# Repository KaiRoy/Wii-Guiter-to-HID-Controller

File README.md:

# HID Guitar Controller - Converting a Wii Guitar into a Windows Compatible HID Device

	<!-- Add image of the PCB -->

## Table of Contents

- [Description](#description)
- [Design](#design)
- [Current State](#current-state-of-the-project)
- [Post Project Notes](#post-project-notes)
- [Installation](#installation) <!-- Should I have Installation and Usage above or below the Design, Current State, Changes, etc? -->
- [Usage](#usage)
- [Credits](#credits)
- [License](#license)

## Description

This project aims to create a device that will take the data from a Wii Guitar Extension Controller and transmit that data to a computer as an HID Device. 

I am a fan of Guitar Hero and rhythm games in general. Guitar Hero was the first rhythm game I ever played and I played it on the Wii using the extension device that came with the game. I long sold the Wii, but I found out that there was a PC version of Guitar Hero called Clone Hero. Since I still had the extension device so I looked into connecting a Wii Remote to a windows computer. While you are able to connect a Wii controller via bluetooth to a Windows Computer it requires the use of third party uncertified drivers. This requires certain settings to turned off in Windows, such as test-signing. The downside of this is that it triggers anti-cheat softwares in competitive video games such as Valorant, making you unable to play those games with the settings turned off. Since these settings require a Computer Restart everytime they are changed, it makes it tedious to switch between games. 

Since I am an electrical engineering major, I decided to make a device that will practically replace the Wii Remote and be able to read the controller inputs from the Wii Guitar Extension Controller and interface with windows as an HID device. I also wanted to make this a battery-powered bluetooth device to remove any cables while using the controller. 

## Design

A lot of information exists on how the Wii works including how the Wii Remote communicates with extension devices such as the Nunchuk or the Wii Guitar. The communication protocol used is a 3.3V I2C signal(s) with nearly all extension devices having an address of 0x52. By default, the data is encrypted but more ‘modern’ extension devices, such as the Wii Guitar, can be set in a decrypted communication mode using the following I2C sequence:

Start, 0xF0, 0x55, Stop, Start, 0xFB, 0x00, Stop

The data is formatted into 6 bytes with the following bit structure with the default bit value being 1 for all of the buttons, changing to 0 when the button is pressed:

SX and SY refer to the x and y-axis of the analog stick. 
WB refers to the analog whammy bar. 
BD and BU refer to the strum bar. 
BO, BR, BB, BG, and BY refer to the Fretbuttons.
B- and B+ are the final two buttons on the 
TB refer to the analog touch bar which is only found on some Wii Guitars

The block diagram above shows the basic outline for the circuit that will take in the data from the Wii Guitar and output via Bluetooth. The necessary power systems for battery power are also included. 

The ESP32, specifically the ESP32-WROOM-32D module, was chosen for the microcontroller because of its inbuilt Bluetooth Low Energy (BLE) Capability as well as my prior experience with designing custom boards for it from my Senior Design Class. My previous design already had the USB Controller (USB-to-UART Converter) and the ESP32, so the only thing that needed to be added was a Battery Management System (BMS) and a 3.3V Regulator. While the old 3.3V regulator Circuit would have worked, I did not know that at the time so I used TI’s WeBench to make a circuit capable of inputting 3.5V-5V and outputting a stable 5V. The circuit that was recommended used the TPS63001. The BQ24090 was chosen for the BMS circuit as one of the guides that I found used that IC for their own custom microcontroller. Another circuit that was added to the schematic was a reverse current protection circuit using the LM66100.

I chose to use a Vertical USB-C connector for two reasons. One is because USB-C is becoming much more common. The second reason is so that in the future, I can attach the board to a piece of acrylic and have the connector flush or near flush with the acrylic once the board is mounted. This idea of mounting is also why I have the programming button and JST connectors (for the battery and connection to the Wii Guitar) on the bottom of the board. Since the USB-C connector is an SMD component, I decided to have all of the SMD components on the same side, but in order for the USB-C to be placed correctly, I needed the other connectors to sit on the other side. Since this was being assembled by hand having all the SMD components on the same side would make it easier to assemble. 

Three libraries are needed to program the board. The first is the Wire library which is needed to communicate with the Wii Guitar via I2C. The second library is LemmingDev’s ESP32-BLE-Gamepad library. This library makes it very easy to turn an ESP32 into a BLE Gamepad that can connect and send data to the computer. The final library that is needed is a dependence for the ESP32-BLE-Gamepad, the NimBLE-Arduino Library. 

## Current State of the Project

Between running a DRC Check and ordering the PCB, a 3.3V via was moved so that it intersectedthe GND Plane. I attempted to cut the via out of the 3.3V circuit an replace the trace with a wire, but I did not have the correct equipement to do it properly. Thus I have yet to test this specific design. I did have a battery charge module from Adafruit, as well as an ESP32 Microcontroller that I had designed previously (which has the same basic microcontoller circuitry that this design had) so I was able to test the code for functionality. The KiCAD files have been updated, and I plan to add a couple of features before repurchasing the board. 

## Post Project Notes

With this project being under a time limit, one of the things I would do differently is how I managed the project and my time. I would allocate specific times throughout my week and days to work on my project. This will allow me to make better progress throught the entire project timeline, giving me more time to catch errors such as the misplaced via that ultimately made the PCB I initially purchased unuseable. I would also allocate time to work on documentation during the developement of the project so that it is more than just an afterthought at the end of the project. 

I would also spend more time learning how Battery Management IC and systems work as they are a very important part to many modern systems and understanding how to work with them will be beneficial in the future, for both personal and professional projects. 

For future versions of this project, I would like to add the following:
- Whammy Bar Support
- Guitar Tilt Support (This is typically handled by the Wii Remote so accelerameters need to be added to the device)
- The creation of a mounting plate/enclosure for the device that fits into the Wii Remote slot on the Guitar
- Ability to connect to the device via USB or BLE without reuploading the code

A reach idea that I had would be to add audio support to this device. Being able to send audio information via the USB or BLE Connections and outputing that audio via connector on the guitar, which I would have to add. This would require the addition of a DAC and AMP to be integrated into the device. Ideally, the audio connection would be the same as the controller connection, but early version may have them separated. Before attempting to implement this idea into this project, I would make a project involving the creation of a custom Bluetooth DAC/AMP Device. 

## Installation

<!--
What additional EDA libraries and files are needed for this project?
- ESP32
-->

What code libraries and files are needed for this project?
- The Arduino [Wire](https://www.arduino.cc/reference/en/language/functions/communication/wire/) Library
- LemmingDev’s [ESP32-BLE-Gamepad](https://github.com/lemmingDev/ESP32-BLE-Gamepad) Library
- H2zero's [NimBLE-Arduino](https://github.com/h2zero/NimBLE-Arduino/releases/tag/1.4.1) Library

<!--

## Usage

## Features

If your project has a lot of features, list them here.

## Tests

-->

## Credits

Third-Part assests used in this project:
- Code Libraries
  - LemmingDev’s [ESP32-BLE-Gamepad](https://github.com/lemmingDev/ESP32-BLE-Gamepad) Library
  - H2zero's [NimBLE-Arduino](https://github.com/h2zero/NimBLE-Arduino/releases/tag/1.4.1) Library
- EDA Libraries/Files
  - Files pulled from 

Tutorials that I followed:
- Predictable Design's [How to Design a Battery Charger Circuit](https://www.youtube.com/watch?v=XBKOkvwgwNw)

## License

Licensed under the [CERN-OHL-S-2.0](LICENSE.txt) License

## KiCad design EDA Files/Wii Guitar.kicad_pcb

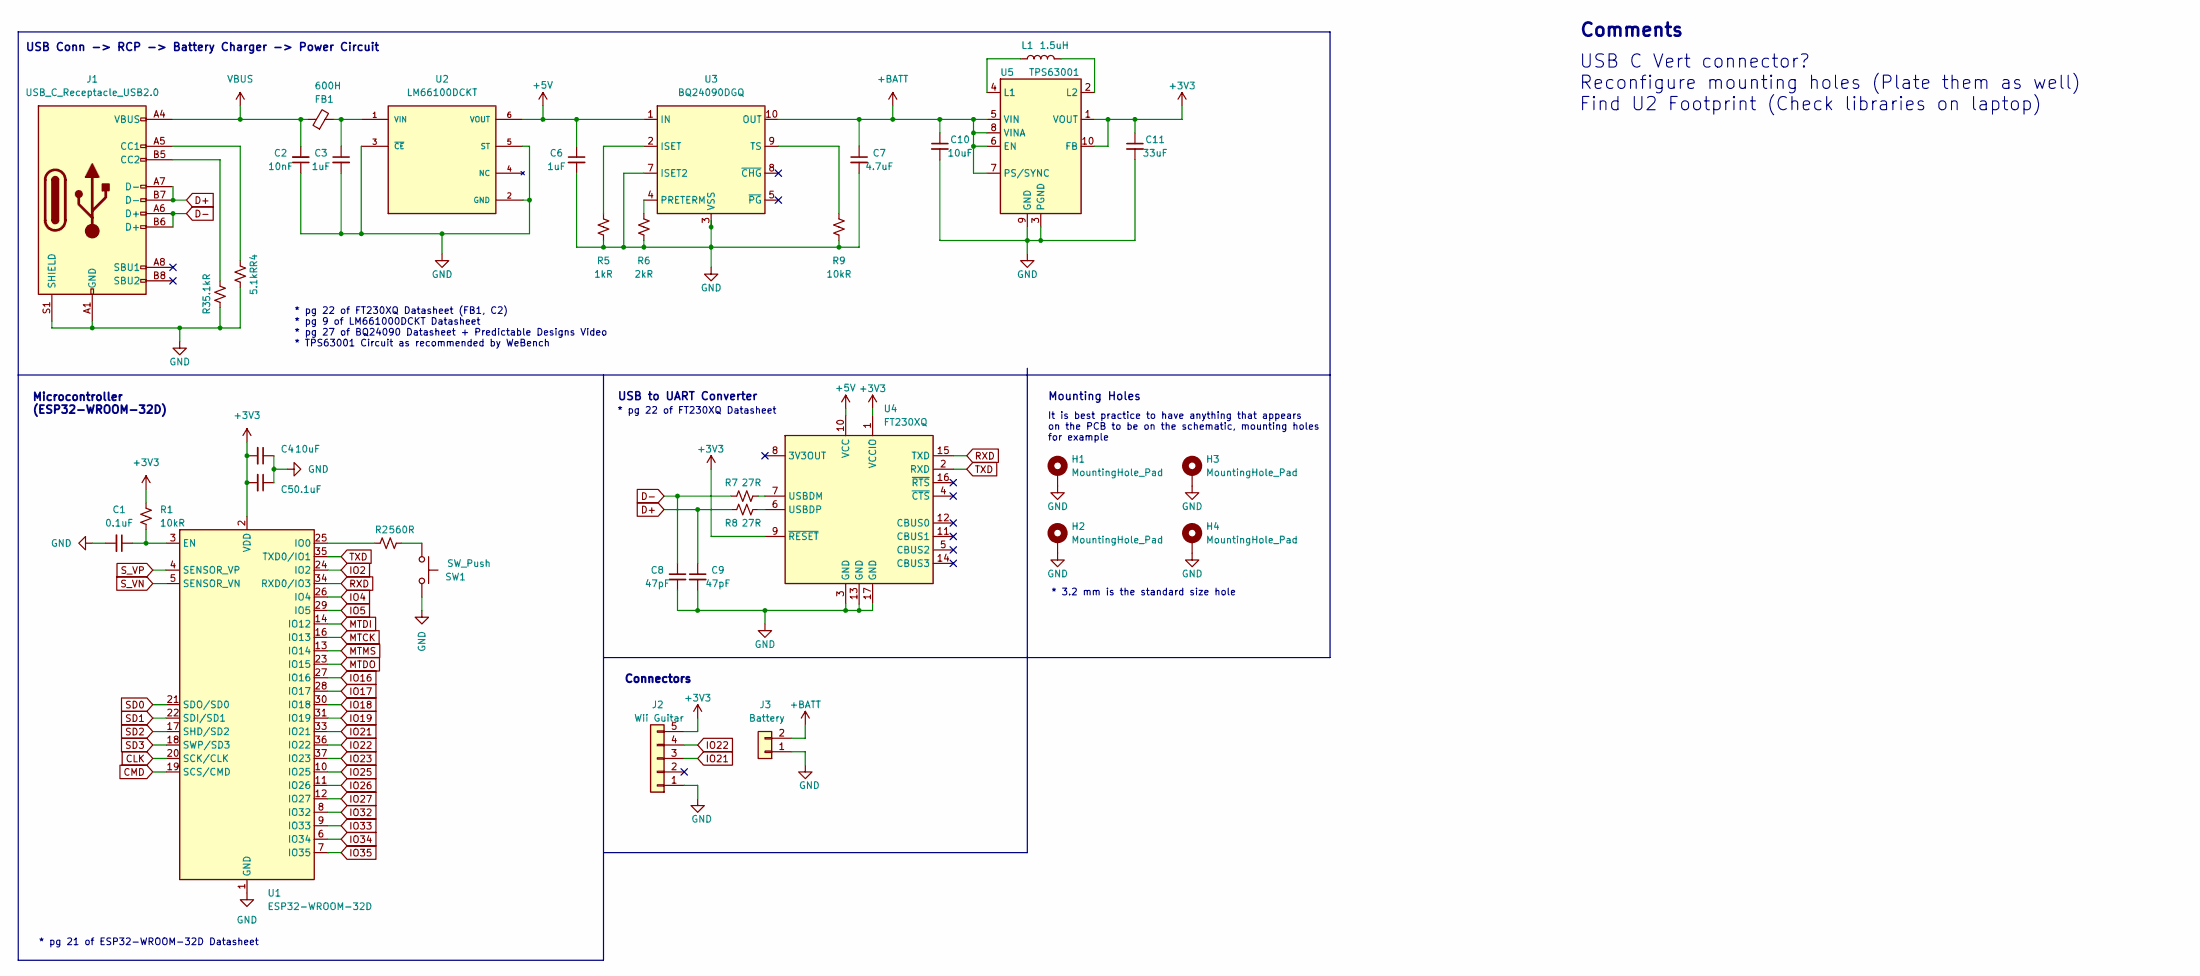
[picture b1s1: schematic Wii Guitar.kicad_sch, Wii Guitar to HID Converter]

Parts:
C1, C5: 0.1uF; C_0805_2012Metric_Pad1.18x1.45mm_HandSolder; Digikey 399-C0805C104K5RAC3123CT-ND
C2: 10nF; C_0805_2012Metric_Pad1.18x1.45mm_HandSolder; Digikey 13-CC0805KPX7R9BB103CT-ND
C3, C6: 1uF; C_0805_2012Metric_Pad1.18x1.45mm_HandSolder; Digikey 1276-6471-1-ND
C4, C10: 10uF; C_0805_2012Metric_Pad1.18x1.45mm_HandSolder; Digikey 1276-1096-1-ND
C7: 4.7uF; C_0805_2012Metric_Pad1.18x1.45mm_HandSolder; Digikey 1276-1244-1-ND
C8, C9: 47pF; C_0805_2012Metric_Pad1.18x1.45mm_HandSolder; Digikey 311-1107-1-ND
C11: 33uF; C_0805_2012Metric_Pad1.18x1.45mm_HandSolder; Digikey 445-8238-1-ND
FB1: 600H; L_0805_2012Metric_Pad1.15x1.40mm_HandSolder; Digikey 541-2302-1-ND
H1, H2, H3, H4: MountingHole_Pad; MountingHole_3.2mm_M3_ISO14580_Pad_TopBottom
J1: USB_C_Receptacle_USB2.0; USB_C_Receptacle_JAE_DX07S024WJ1R350; Digikey 670-2949-1-ND
J2: Wii Guitar; JST_PH_B5B-PH-K_1x05_P2.00mm_Vertical
J3: Battery; JST_PH_B2B-PH-K_1x02_P2.00mm_Vertical
L1: 1.5uH; L_Wuerth_MAPI-1610; Digikey 732-78438313015CT-ND
R1, R9: 10kR; R_0805_2012Metric_Pad1.20x1.40mm_HandSolder; Digikey RNCP0805FTD10K0CT-ND
R2: 560R; R_0805_2012Metric_Pad1.20x1.40mm_HandSolder; Digikey 13-RT0805FRE07560RLCT-ND
R3, R4: 5.1kR; R_0805_2012Metric_Pad1.20x1.40mm_HandSolder; Digikey P5.1KDACT-ND
R5: 1kR; R_0805_2012Metric_Pad1.20x1.40mm_HandSolder; Digikey P1.0KBFCT-ND
R6: 2kR; R_0805_2012Metric_Pad1.20x1.40mm_HandSolder; Digikey P2.0KBSCT-ND
R7, R8: 27R; R_0805_2012Metric_Pad1.20x1.40mm_HandSolder; Digikey 738-RMCF0805FT27R0CT-ND
SW1: SW_Push; SW_PUSH_6mm; Digikey 486-3458-ND
U1: ESP32-WROOM-32D; ESP32-WROOM-32; Digikey 1965-ESP32-WROOM-32D(4MBHIGHTEMP)CT-ND
U2: LM66100DCKT; SOT-363_SC-70-6; PARTREV Rev. A; Digikey 296-53540-1-ND
U3: BQ24090DGQ; HVSSOP-10-1EP_3x3mm_P0.5mm_EP1.57x1.88mm_ThermalVias
U4: FT230XQ; QFN-16-1EP_4x4mm_P0.65mm_EP2.1x2.1mm; Digikey 768-1130-1-ND
U5: TPS63001; Texas_DRC0010J_ThermalVias

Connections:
+3V3: C4.2, C5.2, C11.1, J2.5, R1.1, U1.2 (VDD), U4.1 (VCCIO), U4.9 (~RESET), U5.1 (VOUT), U5.10 (FB)
+5V: C6.1, U2.6 (VOUT), U3.1 (IN), U4.10 (VCC)
+BATT: C7.1, C10.1, J3.2, U3.10 (OUT), U5.5 (VIN), U5.6 (EN), U5.7 (PS/SYNC), U5.8 (VINA)
CLK: U1.20 (SCK/CLK)
CMD: U1.19 (SCS/CMD)
D+: C9.1, J1.A7 (D-), J1.B7 (D-), R8.2
D-: C8.1, J1.A6 (D+), J1.B6 (D+), R7.2
GND: C1.2, C2.1, C3.2, C4.1, C5.1, C6.2, C7.2, C8.2, C9.2, C10.2, C11.2, H1.1, H2.1, H3.1, H4.1, J1.A1 (GND), J1.A12 (GND), J1.B1 (GND), J1.B12 (GND), J1.S1 (SHIELD), J2.1, J3.1, R3.2, R4.1, R5.2, R6.1, R9.1, SW1.2, U1.1 (GND), U1.15 (GND), U1.38 (GND), U1.39 (GND), U2.2 (GND), U2.3 (~CE), U2.5 (ST), U3.3 (VSS), U3.7 (ISET2), U3.11 (VSS), U4.3 (GND), U4.13 (GND), U4.17 (GND), U5.3 (PGND), U5.9 (GND), U5.11 (PGND)
IO2: U1.24 (IO2)
IO4: U1.26 (IO4)
IO5: U1.29 (IO5)
IO16: U1.27 (IO16)
IO17: U1.28 (IO17)
IO18: U1.30 (IO18)
IO19: U1.31 (IO19)
IO21: J2.3, U1.33 (IO21)
IO22: J2.4, U1.36 (IO22)
IO23: U1.37 (IO23)
IO25: U1.10 (IO25)
IO26: U1.11 (IO26)
IO27: U1.12 (IO27)
IO32: U1.8 (IO32)
IO33: U1.9 (IO33)
IO34: U1.6 (IO34)
IO35: U1.7 (IO35)
MTCK: U1.16 (IO13)
MTDI: U1.14 (IO12)
MTDO: U1.23 (IO15)
MTMS: U1.13 (IO14)
unnamed: C1.1, R1.2, U1.3 (EN)
unnamed: C3.1, FB1.2, U2.1 (VIN)
unnamed: J1.A5 (CC1), R4.2
unnamed: J1.B5 (CC2), R3.1
unnamed: L1.1, U5.4 (L1)
unnamed: L1.2, U5.2 (L2)
unnamed: R2.1, U1.25 (IO0)
unnamed: R2.2, SW1.1
unnamed: R5.1, U3.2 (ISET)
unnamed: R6.2, U3.4 (PRETERM)
unnamed: R7.1, U4.7 (USBDM)
unnamed: R8.1, U4.6 (USBDP)
unnamed: R9.2, U3.9 (TS)
RXD: U1.34 (RXD0/IO3), U4.15 (TXD)
SD0: U1.21 (SDO/SD0)
SD1: U1.22 (SDI/SD1)
SD2: U1.17 (SHD/SD2)
SD3: U1.18 (SWP/SD3)
S_VN: U1.5 (SENSOR_VN)
S_VP: U1.4 (SENSOR_VP)
TXD: U1.35 (TXD0/IO1), U4.2 (RXD)
VBUS: C2.2, FB1.1, J1.A4 (VBUS), J1.A9 (VBUS), J1.B4 (VBUS), J1.B9 (VBUS)

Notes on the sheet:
USB Conn -> RCP -> Battery Charger -> Power Circuit
Comments
USB to UART Converter
Connectors
It is best practice to have anything that appears on the PCB to be on the schematic, mounting holes for example
* pg 22 of FT230XQ Datasheet (FB1, C2) * pg 9 of LM661000DCKT Datasheet * pg 27 of BQ24090 Datasheet + Predictable Designs Video * TPS63001 Circuit as recommended by WeBench
USB C Vert connector? Reconfigure mounting holes (Plate them as well) Find U2 Footprint (Check libraries on laptop)
* pg 22 of FT230XQ Datasheet
Mounting Holes
* pg 21 of ESP32-WROOM-32D Datasheet
Microcontroller (ESP32-WROOM-32D)
* 3.2 mm is the standard size hole

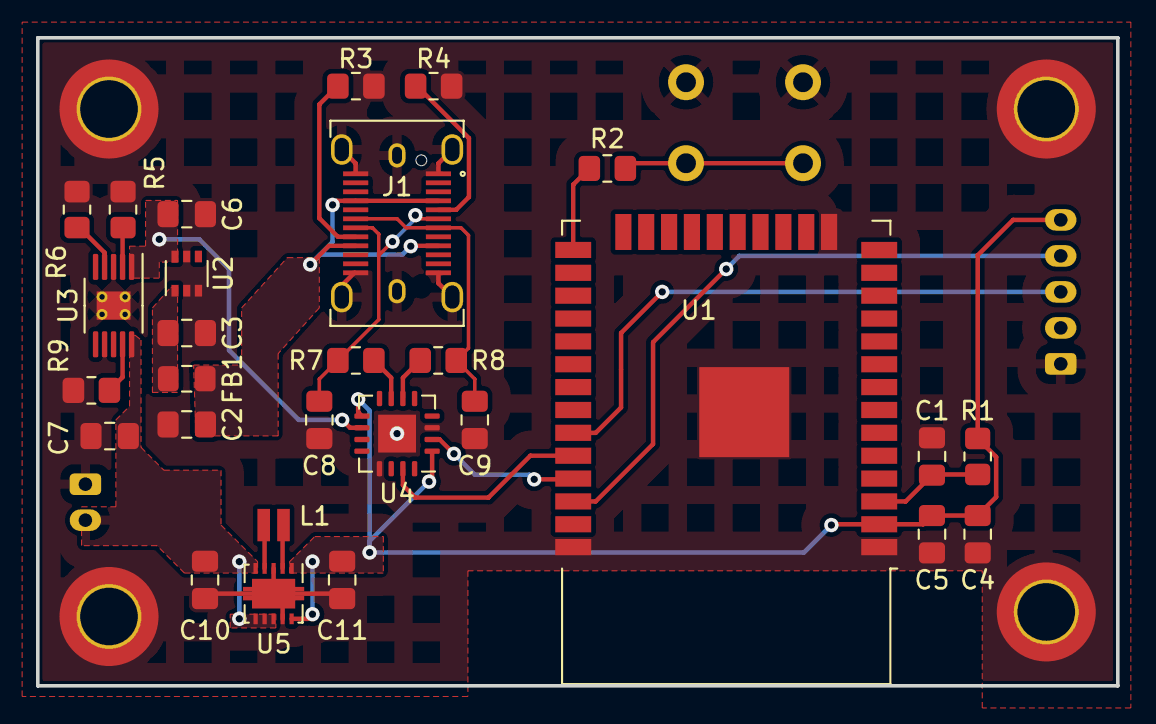
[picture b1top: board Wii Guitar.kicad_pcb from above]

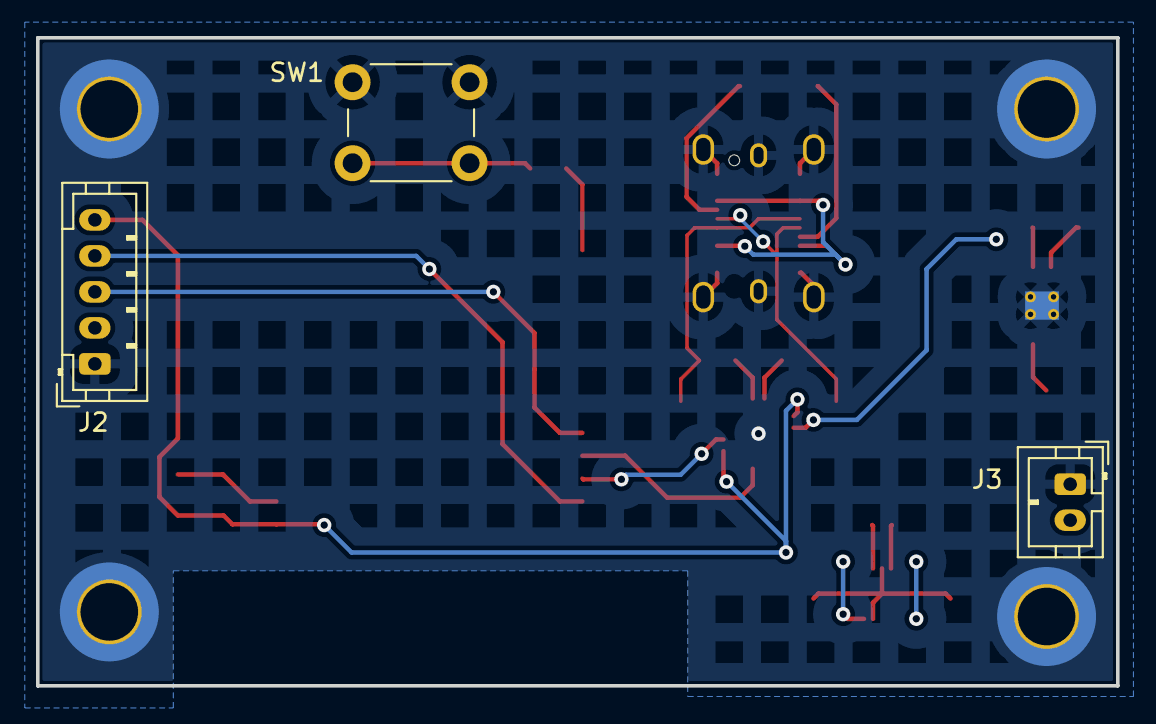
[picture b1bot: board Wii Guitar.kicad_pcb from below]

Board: 2 copper layers, 60.0 x 36.0 mm, 35 parts (3 on the bottom side), 24 nets.

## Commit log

2023-02-16 Added existing files
2023-02-26 Added Final Design
2023-04-09 Reorganized files
2023-04-14 Changed Folders, added Code
2023-04-14 Uploaded Images for README
2023-04-14 Added Images
2023-04-14 Add Images to README
2023-04-26 Added license information
2023-05-04 Update PCB Image in README
